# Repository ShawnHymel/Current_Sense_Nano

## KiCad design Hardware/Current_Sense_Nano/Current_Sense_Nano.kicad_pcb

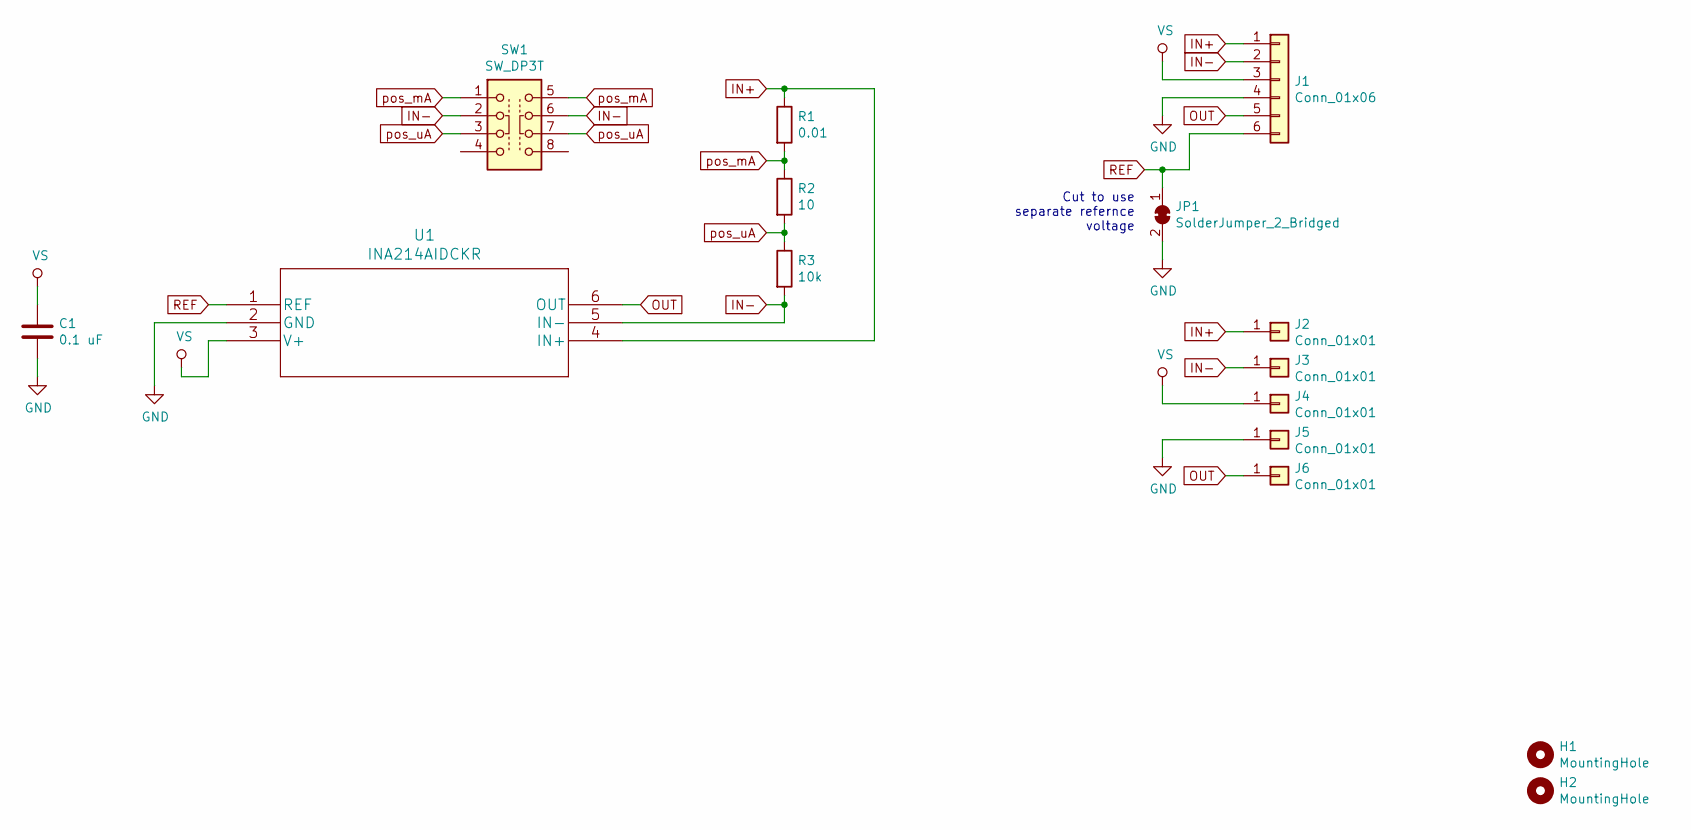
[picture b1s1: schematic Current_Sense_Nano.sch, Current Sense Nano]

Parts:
C1: 0.1 uF; C_0603_1608Metric; Digi-Key_PN 1276-1000-1-ND
H1, H2: MountingHole; MountingHole_3.2mm_M3
J1: Conn_01x06; PinHeader_1x06_P2.54mm_Vertical_NoSilk; Digi-Key_PN 609-3263-ND
J2, J3, J4, J5, J6: Conn_01x01; z_BBC-BIT
JP1: SolderJumper_2_Bridged; SolderJumper-2_P1.3mm_Bridged_RoundedPad1.0x1.5mm
R1: 0.01; R_0805_2012Metric; Digi-Key_PN P124401CT-ND
R2: 10; R_0805_2012Metric; Digi-Key_PN A110351CT-ND
R3: 10k; R_0805_2012Metric; Digi-Key_PN P10KBSCT-ND
SW1: SW_DP3T; Switch_Slide_20.7x10.4mm_G-128S-0157; Digi-Key_PN CWI424-ND
U1: INA214AIDCKR; Digi-Key_PN 296-38956-1-ND

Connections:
GND: C1.2, J1.4, J5.1, JP1.2 (B), U1.2 (GND)
IN+: J1.1, J2.1, R1.1, U1.4 (IN+)
IN-: J1.2, J3.1, R3.2, SW1.2, SW1.6, U1.5 (IN-)
OUT: J1.5, J6.1, U1.6 (OUT)
REF: J1.6, JP1.1 (A), U1.1 (REF)
VS: C1.1, J1.3, J4.1, U1.3 (V+)
pos_mA: R1.2, R2.1, SW1.1, SW1.5
pos_uA: R2.2, R3.1, SW1.3, SW1.7

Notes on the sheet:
Cut to use separate refernce voltage

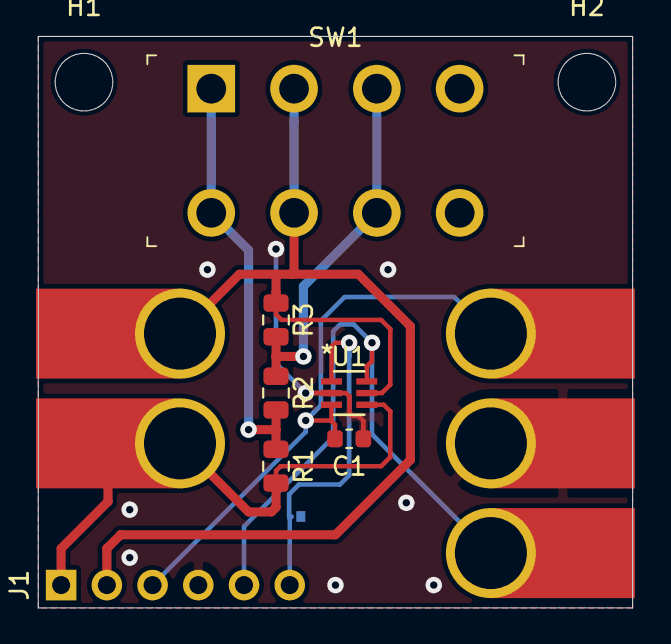
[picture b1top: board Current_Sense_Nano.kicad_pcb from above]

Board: 2 copper layers, 33.0 x 31.8 mm, 15 parts (1 on the bottom side), 8 nets.

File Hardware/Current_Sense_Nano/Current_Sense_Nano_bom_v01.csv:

Component,Description,Part,References,Value,Footprint,Quantity Per PCB,Datasheet,Digi-Key_PN
1,Unpolarized capacitor,C,C1,0.1 uF,,1,~,1276-1000-1-ND
2,"Generic connector, single row, 01x06, script generated (kicad-library-utils/schlib/autogen/connector/)",Conn_01x06,J1,Conn_01x06,,1,~,609-3263-ND
3,Resistor,R,R1,0.01,,1,~,P124401CT-ND
4,Resistor,R,R2,10,,1,~,A110351CT-ND
5,Resistor,R,R3,10k,,1,~,P10KBSCT-ND
6,,SW_DP3T,SW1,SW_DP3T,,1,,CWI424-ND
7,,INA214AIDCKR,U1,INA214AIDCKR,DCK6,1,,296-38956-1-ND





Component Groups:,7
Component Count:,7
Fitted Components:,7
Number of PCBs:,1
Total components:,7
Schematic Version:,v01
Schematic Date:,2019-08-25
PCB Variant:,['default']
BoM Date:,8/25/2019 8:59:35 PM
Schematic Source:,C:\Users\sgmustadio\Documents\GitHub\Current_Sense_Nano\Hardware\Current_Sense_Nano\Current_Sense_Nano.sch
KiCad Version:,Eeschema (5.1.0)-1

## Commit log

2019-08-26 Added components to schematic
2019-09-01 Added switch footprint
2019-09-03 v01 layout complete
2019-09-07 v01 - for milling

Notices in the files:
Hardware/Current_Sense_Nano/Current_Sense_Nano.kicad_pcb:
License: CC BY 4.0
Hardware/Current_Sense_Nano/Current_Sense_Nano.sch:
creativecommons.org/licenses/by/4.0
parts and their libraries:
Copyright 2016 Accelerated Designs. All rights reserved.
